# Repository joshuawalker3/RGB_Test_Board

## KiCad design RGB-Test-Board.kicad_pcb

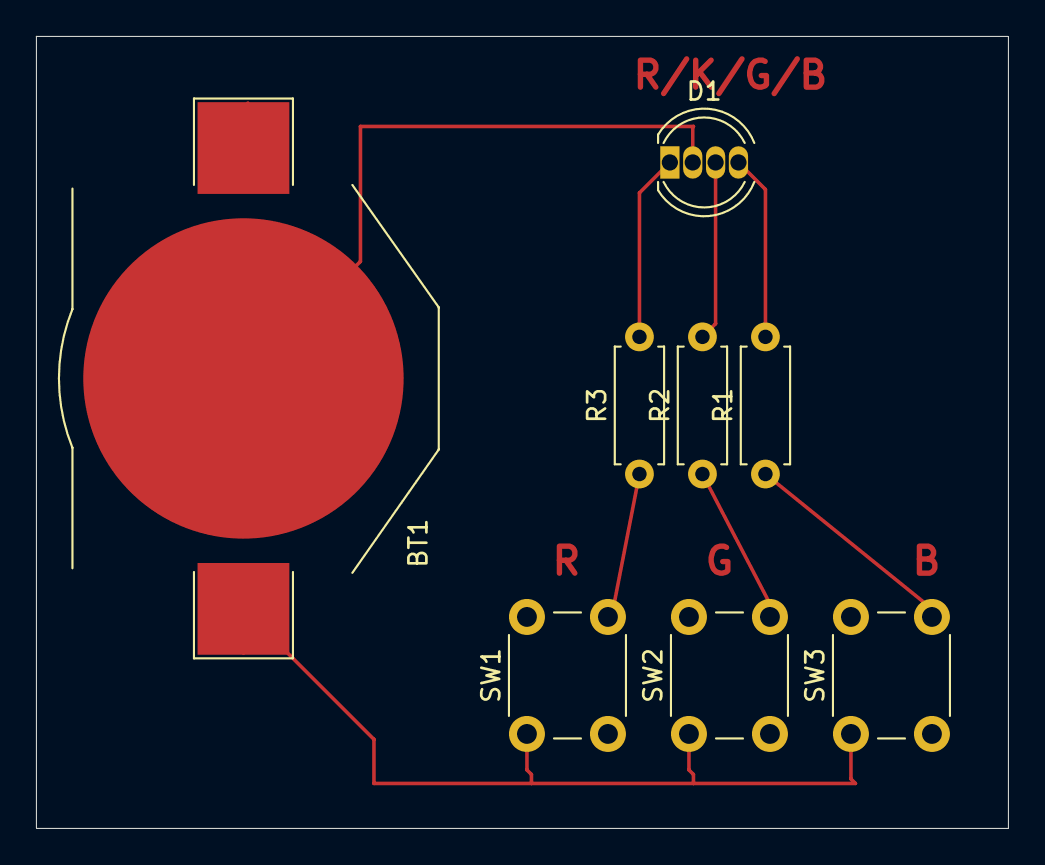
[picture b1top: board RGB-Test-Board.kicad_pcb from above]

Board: 2 copper layers, 54.0 x 44.0 mm, 8 parts (0 on the bottom side), 5 nets.

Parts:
BT1: Battery_Cell; BatteryHolder_Keystone_3002_1x2032
D1: LED_RKGB; LED_D5.0mm-4_RGB
R1, R2, R3: 100; R_Axial_DIN0207_L6.3mm_D2.5mm_P7.62mm_Horizontal
SW1, SW2, SW3: SW_MEC_5E; SW_PUSH_6mm

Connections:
unnamed: BT1.1 (+), SW1.1, SW2.1, SW3.1
unnamed: BT1.2 (-), D1.2 (K)
unnamed: D1.4 (BA), R1.2
unnamed: D1.3 (GA), R2.2
unnamed: D1.1 (RA), R3.2

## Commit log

2024-06-19 First custom pcb
